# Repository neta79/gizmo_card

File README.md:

GizmoCard is my business card. 

It is also a gadget that runs Python:

- fully programmable;
- with Wi-Fi and BLE support;
- an USB port to plug it into a computer and do things with it;
- and a catchy matrix display for good measure.

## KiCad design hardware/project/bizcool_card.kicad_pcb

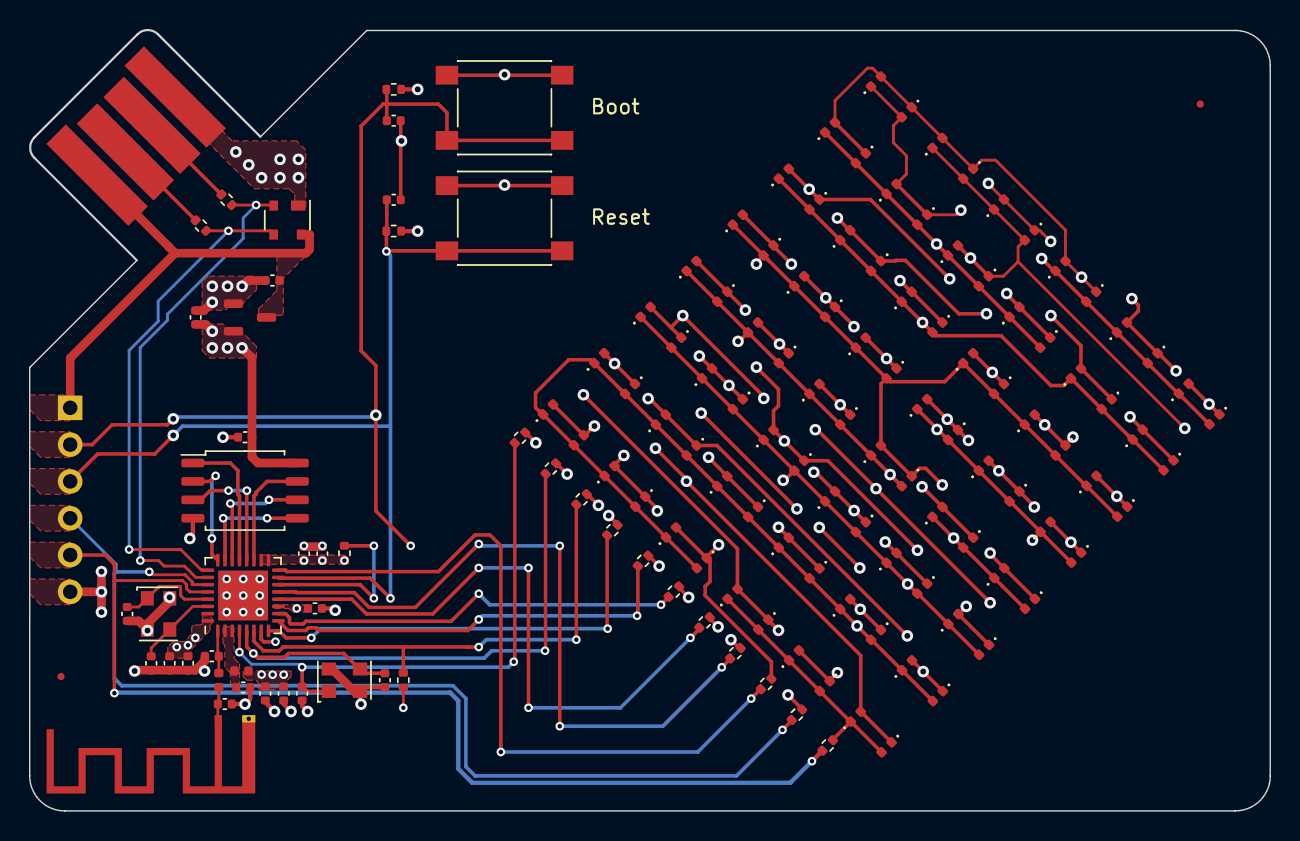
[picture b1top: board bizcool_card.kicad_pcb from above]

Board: 4 copper layers, 85.6 x 53.9 mm, 147 parts (0 on the bottom side), 43 nets.

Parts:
AN1: PCB Antenna; Texas_SWRA117D_2.4GHz_Right
C1, C2, C17, C18: 18pF; C_0402_1005Metric
C3, C4: TBD; C_0402_1005Metric
C5, C6, C7, C10, C13: 1uF; C_0402_1005Metric
C8, C9, C15, C19: 100nF; C_0402_1005Metric
C11, C12, C14, C16: 10nF; C_0402_1005Metric
D1, D2, D3, D4, D5, D6, D7, D8, D9, D10, D11, D12, D13, D14, D15, D16, D17, D18, D19, D20, D21, D22, D23, D24, D25, D26, D27, D28, D29, D30, D31, D32, D33, D34, D35, D36, D37, D38, D39, D40, D41, D42, D43, D44, D45, D46, D47, D48, D49, D50, D51, D52, D53, D54, D55, D56, D57, D58, D59, D60, D61, D62, D63, D64, D65, D66, D67, D68, D69, D70, D71, D72, D73, D74, D75, D76, D77, D78, D79, D80, D81, D82, D83, D84, D85, D86, D87, D88, D89, D90, D91, D92, D93, D94, D95, D96: LED XL-1005SURC; LED_0402_1005Metric
J1: XL-1005SURC; PCB_USB_A_Male_Plug
J2: Conn_01x03; PinHeader_1x06_P2.54mm_Vertical
L1: TBD; L_0402_1005Metric
L2: 2nH 500mA; L_0402_1005Metric
R1, R2: 22R; R_0402_1005Metric
R5, R8, R20, R21: 10K; R_0402_1005Metric
R9, R10, R11, R12, R13, R14, R15, R16, R17, R18, R19: 150; R_0402_1005Metric
REF1, REF2: Fiducial_0.5mm_Mask1mm
SW1, SW2: SW_Push; SW_Push_1P1T_NO_6x6mm_H9.5mm
U1: PRTR5V0U2X; SOT-143
U2: H7233-1; SOT-23-3
U3: ESP32-C3FN4; QFN-32-1EP_5x5mm_P0.5mm_EP3.45x3.45mm
U4: W25Q128JVSIQ; SOIC-8_5.23x5.23mm_P1.27mm
XTAL1: 40MHz; Oscillator_SMD_EuroQuartz_XO32-4Pin_3.2x2.5mm
XTAL2: 32.768 kHz; Oscillator_SMD_EuroQuartz_XO32-4Pin_3.2x2.5mm

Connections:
/CHIP_BOOT: C16.1, J2.3, R5.2, SW2.2, U3.15 (GPIO9/BOOT)
/CHIP_RESET: C15.1, J2.2, R8.2, SW1.2, U3.7 (CHIP_EN)
/MEM_CK: U3.22 (SPICLK/GPIO15), U4.6 (CLK)
/MEM_CS: U3.21 (SPICS0/GPIO14), U4.1 (~CS)
/MEM_IO0: U3.23 (SPID/GPIO16), U4.5 (DI(IO0))
/MEM_IO1: U3.24 (SPIQ/GPIO17), U4.2 (DO(IO1))
/MEM_IO2: U3.20 (SPIWP/GPIO13), U4.3 (IO2)
/MEM_IO3: U3.19 (SPIHD/GPIO12), U4.7 (IO3)
/MX_R0: C17.1, R9.1, U3.4 (XTAL_32K_P/ADC1_CH0), XTAL2.1
/MX_R1: C18.2, R10.1, U3.5 (XTAL_32K_N/ADC1_CH1), XTAL2.3
/MX_R2: R11.1, R20.1, U3.6 (GPIO2/ADC1_CH2)
/MX_R3: R12.1, U3.8 (GPIO3/ADC1_CH3)
/MX_R4: R13.1, U3.9 (MTMS/GPIO4/ADC1_CH4)
/MX_R5: R14.1, U3.10 (MTDI/GPIO5/ADC2_CH0)
/MX_R6: R15.1, U3.12 (MTCK/GPIO6)
/MX_R7: R16.1, U3.13 (MTDO/GPIO7)
/MX_R8: R17.1, U3.16 (GPIO10)
/MX_R9: J2.4, R18.1, U3.27 (U0RXD/GPIO20)
/MX_R10: J2.5, R19.1, U3.28 (U0TXD/GPIO21)
/USB_DN: R1.2, U1.3 (I/O2), U3.25 (GPIO18/USB_D-)
/USB_DP: R2.2, U1.2 (I/O1), U3.26 (GPIO19/USB_D+)
/VDD3_3: C6.1, C7.1, C8.1, C10.1, C11.1, C12.1, C13.1, C14.1, C19.1, L2.1, R5.1, R8.1, R20.2, R21.2, U2.2 (VO), U3.11 (VDD3P3_RTC), U3.17 (VDD3P3_CPU), U3.18 (VDD_SPI/GPIO11), U3.31 (VDDA), U3.32 (VDDA), U4.8 (VCC)
/VDD3_3_RF: C9.1, L2.2, U3.2 (VDD3P3), U3.3 (VDD3P3)
/VUSB: C5.1, J1.1, J2.1, U1.4 (VCC), U2.3 (VI)
/XTAL_CORE_N: C1.1, U3.29 (XTAL_N), XTAL1.1
/XTAL_CORE_P: C2.2, U3.30 (XTAL_P), XTAL1.3
GND: C1.2, C2.1, C3.2, C4.2, C5.2, C6.2, C7.2, C8.2, C9.2, C10.2, C11.2, C12.2, C13.2, C14.2, C15.2, C16.2, C17.2, C18.1, C19.2, J1.4, J2.6, SW1.1, SW2.1, U1.1 (GND), U2.1 (GND), U3.33 (GND), U4.4 (GND), XTAL1.2, XTAL1.4, XTAL2.2, XTAL2.4
unnamed: AN1.1 (A), C4.1, L1.1
unnamed: D1.2 (A), D2.1 (K), D3.2 (A), D4.1 (K), D7.2 (A), D8.1 (K), D13.2 (A), D14.1 (K), D21.2 (A), D22.1 (K), D31.2 (A), D32.1 (K), D43.2 (A), D44.1 (K), D57.2 (A), D58.1 (K), D73.2 (A), D74.1 (K), D91.2 (A), D92.1 (K), R9.2
unnamed: D1.1 (K), D2.2 (A), D5.2 (A), D6.1 (K), D9.2 (A), D10.1 (K), D15.2 (A), D16.1 (K), D23.2 (A), D24.1 (K), D33.2 (A), D34.1 (K), D45.2 (A), D46.1 (K), D59.2 (A), D60.1 (K), D75.2 (A), D76.1 (K), D93.2 (A), D94.1 (K), R10.2
unnamed: D7.1 (K), D8.2 (A), D9.1 (K), D10.2 (A), D11.1 (K), D12.2 (A), D19.2 (A), D20.1 (K), D27.2 (A), D28.1 (K), D37.2 (A), D38.1 (K), D49.2 (A), D50.1 (K), D63.2 (A), D64.1 (K), D79.2 (A), D80.1 (K), R12.2
unnamed: D3.1 (K), D4.2 (A), D5.1 (K), D6.2 (A), D11.2 (A), D12.1 (K), D17.2 (A), D18.1 (K), D25.2 (A), D26.1 (K), D35.2 (A), D36.1 (K), D47.2 (A), D48.1 (K), D61.2 (A), D62.1 (K), D77.2 (A), D78.1 (K), D95.2 (A), D96.1 (K), R11.2
unnamed: D13.1 (K), D14.2 (A), D15.1 (K), D16.2 (A), D17.1 (K), D18.2 (A), D19.1 (K), D20.2 (A), D29.2 (A), D30.1 (K), D39.2 (A), D40.1 (K), D51.2 (A), D52.1 (K), D65.2 (A), D66.1 (K), D81.2 (A), D82.1 (K), R13.2
unnamed: D21.1 (K), D22.2 (A), D23.1 (K), D24.2 (A), D25.1 (K), D26.2 (A), D27.1 (K), D28.2 (A), D29.1 (K), D30.2 (A), D41.2 (A), D42.1 (K), D53.2 (A), D54.1 (K), D67.2 (A), D68.1 (K), D83.2 (A), D84.1 (K), R14.2
unnamed: D31.1 (K), D32.2 (A), D33.1 (K), D34.2 (A), D35.1 (K), D36.2 (A), D37.1 (K), D38.2 (A), D39.1 (K), D40.2 (A), D41.1 (K), D42.2 (A), D55.2 (A), D56.1 (K), D69.2 (A), D70.1 (K), D85.2 (A), D86.1 (K), R15.2
unnamed: D43.1 (K), D44.2 (A), D45.1 (K), D46.2 (A), D47.1 (K), D48.2 (A), D49.1 (K), D50.2 (A), D51.1 (K), D52.2 (A), D53.1 (K), D54.2 (A), D55.1 (K), D56.2 (A), D71.2 (A), D72.1 (K), D87.2 (A), D88.1 (K), R16.2
unnamed: D57.1 (K), D58.2 (A), D59.1 (K), D60.2 (A), D61.1 (K), D62.2 (A), D63.1 (K), D64.2 (A), D65.1 (K), D66.2 (A), D67.1 (K), D68.2 (A), D69.1 (K), D70.2 (A), D71.1 (K), D72.2 (A), D89.2 (A), D90.1 (K), R17.2
unnamed: D73.1 (K), D74.2 (A), D75.1 (K), D76.2 (A), D77.1 (K), D78.2 (A), D79.1 (K), D80.2 (A), D81.1 (K), D82.2 (A), D83.1 (K), D84.2 (A), D85.1 (K), D86.2 (A), D87.1 (K), D88.2 (A), D89.1 (K), D90.2 (A), R18.2
unnamed: D91.1 (K), D92.2 (A), D93.1 (K), D94.2 (A), D95.1 (K), D96.2 (A), R19.2
unnamed: J1.2, R1.1
unnamed: J1.3, R2.1
unnamed: R21.1, U3.14 (GPIO8)
unnamed: C3.1, L1.2, U3.1 (LNA_IN)

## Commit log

2023-12-11 inital schematic and PCB design
2023-12-11 asset rename
2023-12-11 move debug header out of the way
2023-12-12 changed: script on the back face
2023-12-12 fix: correct LDO component part name
2023-12-12 buried all vias that don't belong to a pad
    hopefully this closes #3
2023-12-12 update: gitignore
2023-12-12 fix: LCSC component references
2023-12-12 fix disconnected cut outline, change push button footprints
    - Edge.Cuts layer was not a properly closed shape
    - adopted quite bulky 6x6 SMT push buttons (still DNP though)
2023-12-12 fix: border connector solder mask, GND trace
2023-12-12 change LDO regulator
    switched to a SOT-23-3 LDO reg, a smaller one (400mA).
    technically not in-spec, should use 2 of these.
2023-12-14 design sent for a test print
2023-12-24 fix: d1-d6 reordering, re-routing
2024-04-20 layout update
